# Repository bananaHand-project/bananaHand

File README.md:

---

**BananaHand** is an open-source 16 DOF/6 DOA humanoid hand designed for physical AI research and deployment on light-weight robot arms.

BananaHand features human-like proportions with no fore-arm, up to 4lb payload capacity, integrated palm and finger tip FSR based force sensing, and a low BOM cost of $900USD.

With the project being open-source as a top priority, all resources used in the creation are freely available and open-source themselves (KiCad, OnShape, Foxglove, Embassy-rs, etc.).

*We're in continuous development and actively seeking contributors, research partners, and company collaborators to shape the next generation of practical humanoid systems. Ready to join the future of open-source robotics?*

## Repo Structure

- [`docs/`](./docs/) contains build instructions, getting started guide, and more.
- [`firmware/`](./firmware/) contains the code that runs on the bananaHand main board.
  - [`firmware/primary-g474/`](./firmware/primary-g474/) contains the firmware run on the primary MCU (stm32g474).
  - [`firmware/sensing-c071/`](./firmware/sensing-c071/) contains the firmware run on the sensing MCU (stm32c071).
  - [`firmware/common/`](./firmware/common/) contains code used by both MCUs.
  - [`firmware/experiments/`](./firmware/experiments/) contains code used in the development of the hand.
- [`hardware/`](./hardware/) contains both electrical and mechanical CAD models, BOMs, and detailed descriptions.
- [`software/`](./software/) contains ROS and Foxglove implementations.

---
***We can't wait to see what you grasp!***

Made with ❤️ in 🇨🇦 at 🪿.

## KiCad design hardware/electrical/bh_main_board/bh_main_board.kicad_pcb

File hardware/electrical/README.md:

# Electrical

The electrical system for bananaHand is built around the main board. The main board is responsible for the following functions: communication with the controlling device, motor control, and FSR sensing. A simplified block diagram describing the main board can be seen below. It requires a single +12V 24W input source and exposes UART, CAN bus, and half-duplex RS485 options for interfacing. Depending on the device you are trying to interface with, a buck converter may be needed to drop your source voltage down to the required 12V.

## Main Board

The main board has the following sub-circuits:

- **Micro-controllers**: There are two MCUs on the main board. The first is the stm32g474, responsible for communication with the upstream device and motor control. The second micro-controller is the stm32c071, which acts as a "smart" ADC, filtering and forwarding force readings to the stm32g4.
- **Power stage**: Basic fuse protection, and a MPM3610 buck converter for 12V -> 3V3 for logic level ICs
- **Motor driving**: There are eight DRV8876 motor driver circuits for the [PQ12P](https://www.actuonix.com/pq12-30-12-p). The driving circuits are controlled and motor positions are read by the stm32g474 micro-controller.
- **Force sensing**: Simple linear voltage divider circuits are used to interface with the force sensitive resistors. Their voltages are read by the 2nd micro-controller on board the stm32c071
- **Communication interfaces**: There are three communication interfaces exposed by the board: CAN Bus, UART, and half-duplex RS485.

### Schematic

A full PDF of the schematic can be found in `bh_main_board/bananaHand_main_board_sch.pdf` or linked [here](./bh_main_board/bananaHand_main_board_sch.pdf).

### Layout

**Four layer:** Sig, GND, GND/PWR, Sig

### Known Flaws

#### V0.1.0

No issues that impact the performance of the board or require re-work.

- The silkscreen on the back labelling the PQ12P connectors for Index1 and Index 2 are flipped.
- Index 2 breaks the convention of the HRTIM channel connections to DRV8876 with `IN1 <-> CH1` and `IN2 <-> CH2` (instead of `IN1 <-> CH2` and `IN2 <-> CH1` like all other fingers).

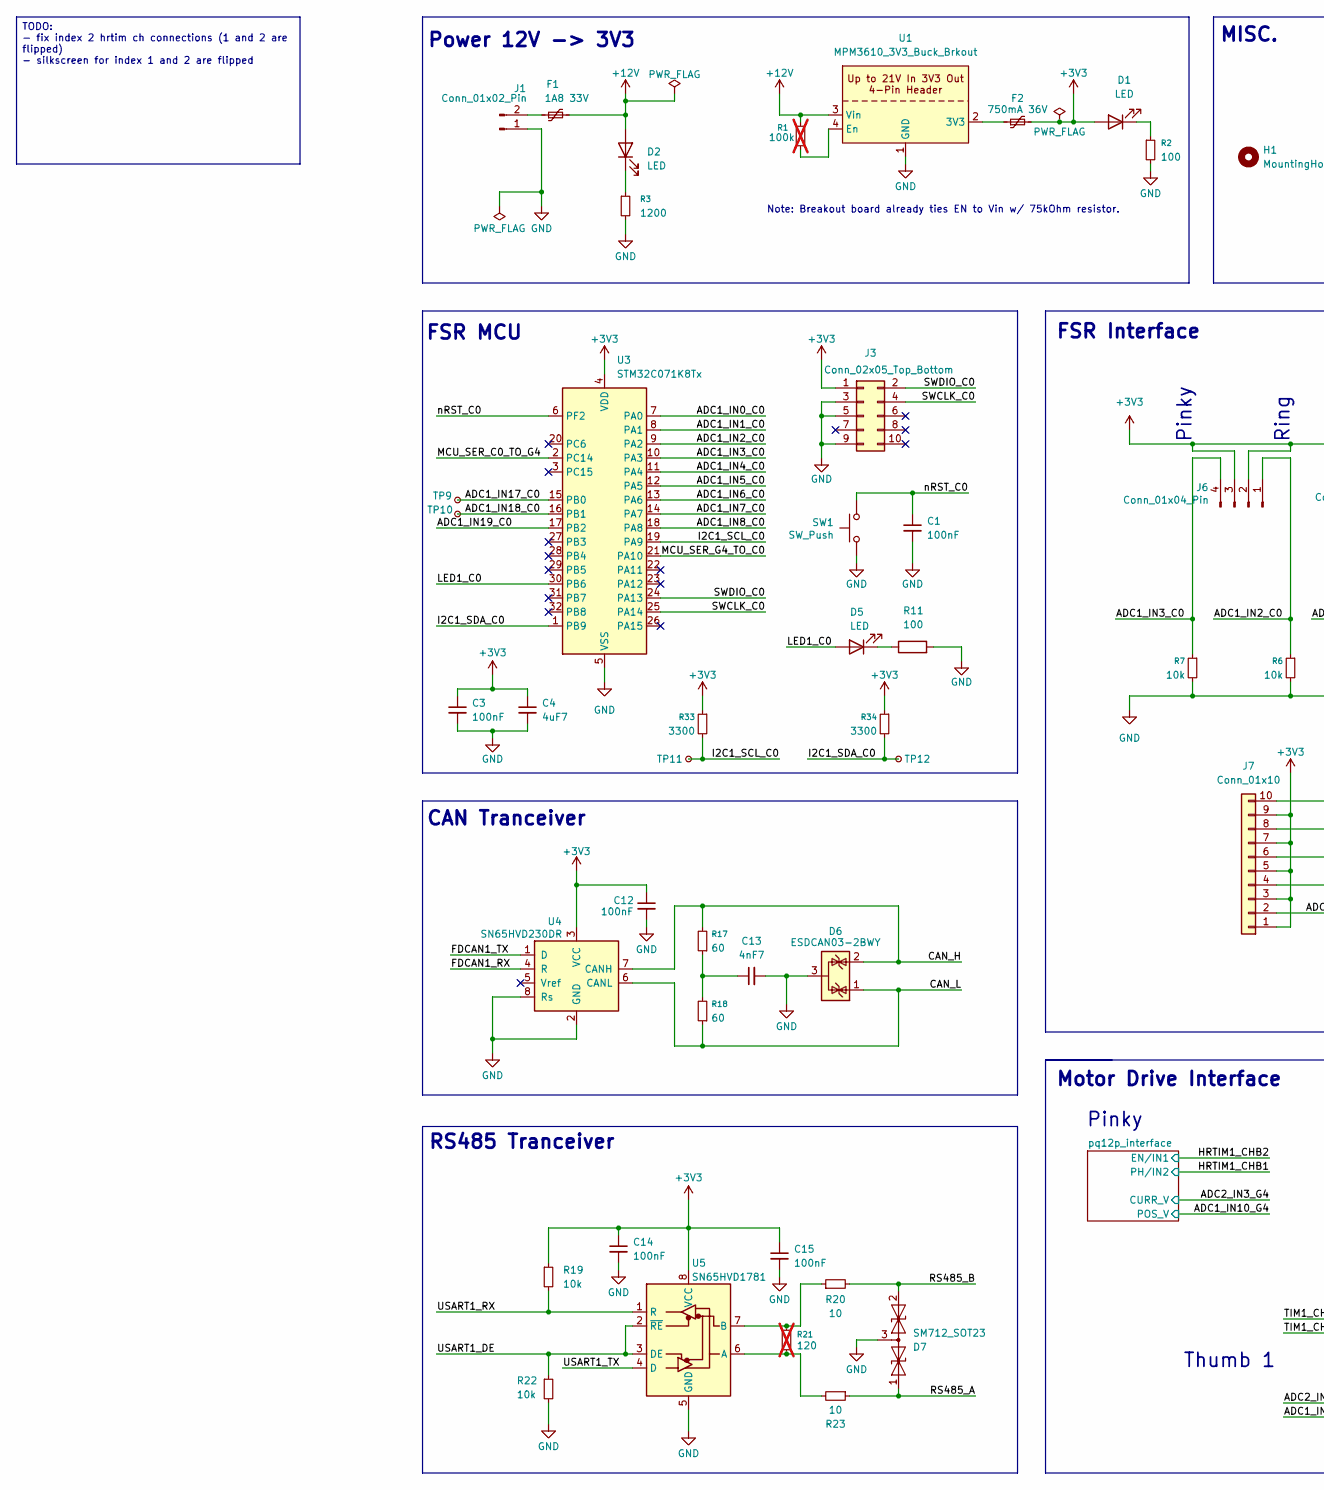
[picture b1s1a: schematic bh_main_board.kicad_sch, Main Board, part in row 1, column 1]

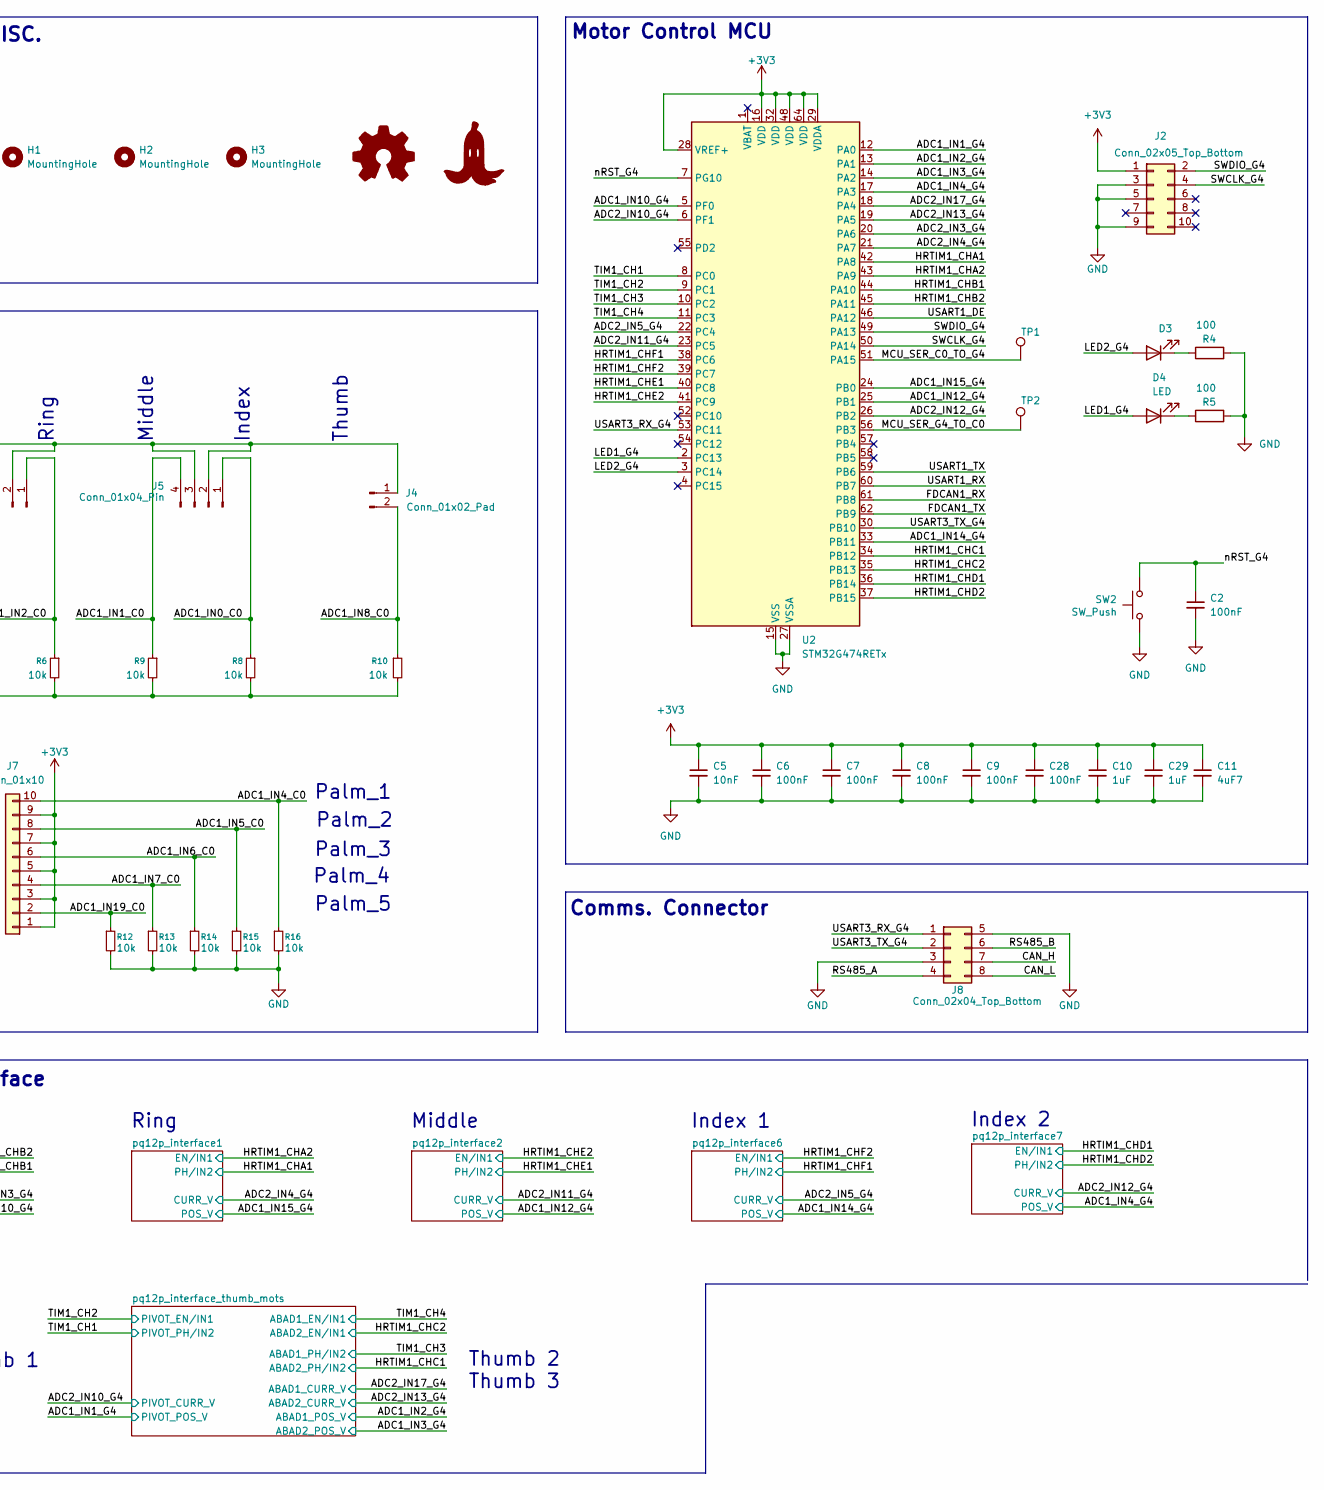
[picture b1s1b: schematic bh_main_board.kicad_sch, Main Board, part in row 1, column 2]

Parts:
ART1: mk_banana_footprint
ART2: Logo_Open_Hardware_Small; OSHW-Logo2_9.8x8mm_SilkScreen
C1, C2, C3, C6, C7, C8, C9, C12, C14, C15, C28: 100nF; C_0402_1005Metric; MFR # GRM155R71H104KE14D; LCSC # C77020
C4, C11: 4uF7; C_0603_1608Metric_Pad1.08x0.95mm_HandSolder; MFR # GRM188R6YA475KE15D; LCSC # C162274
C5: 10nF; C_0402_1005Metric; MFR # GRM155R71H103KA88D; LCSC # C77019
C10, C29: 1uF; C_0603_1608Metric_Pad1.08x0.95mm_HandSolder; MFR # GCM188R71E105KA64D; LCSC # C85862
C13: 4nF7; C_0402_1005Metric; MFR # GRM1555C1H472JE01D; LCSC # C1518204
D1, D2, D3, D4, D5: LED; LED_0402_1005Metric_Pad0.77x0.64mm_HandSolder; MFR # XL-1005UYC; LCSC # C25503856
D6: ESDCAN03-2BWY; SOT-323_SC-70; MFR # ESDCAN03-2BWY; LCSC # C1973833
D7: SM712_SOT23; SOT-23; MFR # SM712-02HTG; LCSC # C172881
F1: 1A8 33V; Fuse_1206_3216Metric_Pad1.42x1.75mm_HandSolder; MFR # YTL 1206L100/33V; LCSC # C49318377
F2: 750mA 36V; Fuse_1206_3216Metric; MFR # 1206L075/36NR; LCSC # C49196638
H1, H2, H3: MountingHole; MountingHole_2.7mm_Pad_Via
J1: Conn_01x02_Pin; AMASS_XT30UPB-M_1x02_P5.0mm_Vertical; MFR # XT30UPB-M; LCSC # C428721
J2, J3: Conn_02x05_Top_Bottom; PinHeader_2x05_P1.27mm_Vertical; MFR # ZX-PZ1.27-2-5PZZ; LCSC # C7501289
J4: Conn_01x02_Pad; JST_ZH_B2B-ZR_1x02_P1.50mm_Vertical; MFR # JST B2B-ZR(LF)(SN); LCSC # C158011
J5, J6: Conn_01x04_Pin; JST_ZH_B4B-ZR_1x04_P1.50mm_Vertical; MFR # JST B4B-ZR(LF)(SN); LCSC # C157997
J7: Conn_01x10; JST_ZH_B10B-ZR_1x10_P1.50mm_Vertical; MFR # B10B-ZR(LF)(SN); LCSC # C158036
J8: Conn_02x04_Top_Bottom; JST_PHD_B8B-PHDSS_2x04_P2.00mm_Vertical; MFR # B8B-PHDSS(LF)(SN); LCSC # C157975
R1: 100k; R_0603_1608Metric_Pad0.98x0.95mm_HandSolder; MFR # RC0603FR-07100KL; LCSC # C14675; not fitted
R2, R4, R5, R11: 100; R_0402_1005Metric_Pad0.72x0.64mm_HandSolder; MFR # ERJ2RKF1000X; LCSC # C413063
R3: 1200; R_0603_1608Metric_Pad0.98x0.95mm_HandSolder; MFR # RC0603FR-071K2L; LCSC # C114605
R6, R7, R8, R9, R10, R12, R13, R14, R15, R16, R19, R22: 10k; R_0402_1005Metric_Pad0.72x0.64mm_HandSolder; MFR # RT0402BRD0710KL; LCSC # C190095
R17, R18: 60; R_0603_1608Metric_Pad0.98x0.95mm_HandSolder; MFR # 0603WAF604JT5E; LCSC # C23090
R20, R23: 10; R_0603_1608Metric_Pad0.98x0.95mm_HandSolder; MFR # RC0603FR-0710RL; LCSC # C109318
R21: 120; R_0603_1608Metric_Pad0.98x0.95mm_HandSolder; MFR # RC0603FR-07120RL; LCSC # C114640; not fitted
R33, R34: 3300; R_0402_1005Metric_Pad0.72x0.64mm_HandSolder; MFR # RC0402FR-073K3L; LCSC # C137992
SW1, SW2: SW_Push; SW_SPST_TS-1088-xR025; MFR # TS-1088R-02526; LCSC # C455281
TP1, TP2: TestPoint; TestPoint_Pad_D1.0mm
TP9, TP10, TP11, TP12: TestPoint_Small; TestPoint_Pad_D2.0mm
U1: MPM3610_3V3_Buck_Brkout; MP3610_3V3_BUCK_BREAKOUT
U2: STM32G474RETx; LQFP-64_10x10mm_P0.5mm; MFR # STM32G474RET6; LCSC # C521608
U3: STM32C071K8Tx; LQFP-32_7x7mm_P0.8mm; MFR # STM32C071K8T6; LCSC # C43650208
U4: SN65HVD230DR; SOIC-8_3.9x4.9mm_P1.27mm; MFR # SN65HVD230DR; LCSC # C12084
U5: SN65HVD1781; SOIC-8_3.9x4.9mm_P1.27mm; MFR # SN65HVD1781DR; LCSC # C42737

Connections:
+3V3: C3.1, C4.1, C5.1, C6.1, C7.1, C8.1, C9.1, C10.1, C11.1, C12.1, C14.1, C15.1, C28.1, C29.1, D1.2 (A), F2.2, J2.1, J3.1, J4.1, J5.2, J5.3, J6.2, J6.3, J7.1, J7.3, J7.5, J7.7, J7.9, R19.1, R33.1, R34.1, U2.16 (VDD), U2.28 (VREF+), U2.29 (VDDA), U2.32 (VDD), U2.48 (VDD), U2.64 (VDD), U3.4 (VDD), U4.3 (VCC), U5.8 (VCC); also elsewhere on the board
+12V: D2.2 (A), F1.2, R1.1, U1.3 (Vin); also elsewhere on the board
/ADC1_IN0_C0: J5.1, R8.1, U3.7 (PA0)
/ADC1_IN1_C0: J5.4, R9.1, U3.8 (PA1)
/ADC1_IN1_G4: U2.12 (PA0); also elsewhere on the board
/ADC1_IN2_C0: J6.1, R6.1, U3.9 (PA2)
/ADC1_IN2_G4: U2.13 (PA1); also elsewhere on the board
/ADC1_IN3_C0: J6.4, R7.1, U3.10 (PA3)
/ADC1_IN3_G4: U2.14 (PA2); also elsewhere on the board
/ADC1_IN4_C0: J7.10, R16.1, U3.11 (PA4)
/ADC1_IN4_G4: U2.17 (PA3); also elsewhere on the board
/ADC1_IN5_C0: J7.8, R15.1, U3.12 (PA5)
/ADC1_IN6_C0: J7.6, R14.1, U3.13 (PA6)
/ADC1_IN7_C0: J7.4, R13.1, U3.14 (PA7)
/ADC1_IN8_C0: J4.2, R10.1, U3.18 (PA8)
/ADC1_IN10_G4: U2.5 (PF0); also elsewhere on the board
/ADC1_IN12_G4: U2.25 (PB1); also elsewhere on the board
/ADC1_IN14_G4: U2.33 (PB11); also elsewhere on the board
/ADC1_IN15_G4: U2.24 (PB0); also elsewhere on the board
/ADC1_IN17_C0: TP9.1, U3.15 (PB0)
/ADC1_IN18_C0: TP10.1, U3.16 (PB1)
/ADC1_IN19_C0: J7.2, R12.1, U3.17 (PB2)
/ADC2_IN3_G4: U2.20 (PA6); also elsewhere on the board
/ADC2_IN4_G4: U2.21 (PA7); also elsewhere on the board
/ADC2_IN5_G4: U2.22 (PC4); also elsewhere on the board
/ADC2_IN10_G4: U2.6 (PF1); also elsewhere on the board
/ADC2_IN11_G4: U2.23 (PC5); also elsewhere on the board
/ADC2_IN12_G4: U2.26 (PB2); also elsewhere on the board
/ADC2_IN13_G4: U2.19 (PA5); also elsewhere on the board
/ADC2_IN17_G4: U2.18 (PA4); also elsewhere on the board
/CAN_H: D6.2 (K), J8.7, R17.2, U4.7 (CANH)
/CAN_L: D6.1 (K), J8.8, R18.1, U4.6 (CANL)
/FDCAN1_RX: U2.61 (PB8), U4.4 (R)
/FDCAN1_TX: U2.62 (PB9), U4.1 (D)
/HRTIM1_CHA1: U2.42 (PA8); also elsewhere on the board
/HRTIM1_CHA2: U2.43 (PA9); also elsewhere on the board
/HRTIM1_CHB1: U2.44 (PA10); also elsewhere on the board
/HRTIM1_CHB2: U2.45 (PA11); also elsewhere on the board
/HRTIM1_CHC1: U2.34 (PB12); also elsewhere on the board
/HRTIM1_CHC2: U2.35 (PB13); also elsewhere on the board
/HRTIM1_CHD1: U2.36 (PB14); also elsewhere on the board
/HRTIM1_CHD2: U2.37 (PB15); also elsewhere on the board
/HRTIM1_CHE1: U2.40 (PC8); also elsewhere on the board
/HRTIM1_CHE2: U2.41 (PC9); also elsewhere on the board
/HRTIM1_CHF1: U2.38 (PC6); also elsewhere on the board
/HRTIM1_CHF2: U2.39 (PC7); also elsewhere on the board
/I2C1_SCL_C0: R33.2, TP11.1, U3.19 (PA9)
/I2C1_SDA_C0: R34.2, TP12.1, U3.1 (PB9)
/LED1_C0: D5.2 (A), U3.30 (PB6)
/LED1_G4: D4.2 (A), U2.2 (PC13)
/LED2_G4: D3.2 (A), U2.3 (PC14)
/MCU_SER_C0_TO_G4: TP1.1, U2.51 (PA15), U3.2 (PC14)
/MCU_SER_G4_TO_C0: TP2.1, U2.56 (PB3), U3.21 (PA10)
/RS485_A: D7.1 (A1), J8.4, R23.1
/RS485_B: D7.2 (A2), J8.6, R20.2
/SWCLK_C0: J3.4, U3.25 (PA14)
/SWCLK_G4: J2.4, U2.50 (PA14)
/SWDIO_C0: J3.2, U3.24 (PA13)
/SWDIO_G4: J2.2, U2.49 (PA13)
/TIM1_CH1: U2.8 (PC0); also elsewhere on the board
/TIM1_CH2: U2.9 (PC1); also elsewhere on the board
/TIM1_CH3: U2.10 (PC2); also elsewhere on the board
/TIM1_CH4: U2.11 (PC3); also elsewhere on the board
/USART1_DE: R22.1, U2.46 (PA12), U5.2 (~RE), U5.3 (DE)
/USART1_RX: R19.2, U2.60 (PB7), U5.1 (R)
/USART1_TX: U2.59 (PB6), U5.4 (D)
/USART3_RX_G4: J8.1, U2.53 (PC11)
/USART3_TX_G4: J8.2, U2.30 (PB10)
/nRST_C0: C1.1, SW1.2, U3.6 (PF2)
/nRST_G4: C2.1, SW2.2, U2.7 (PG10)
GND: C1.2, C2.2, C3.2, C4.2, C5.2, C6.2, C7.2, C8.2, C9.2, C10.2, C11.2, C12.2, C13.2, C14.2, C15.2, C28.2, C29.2, D6.3 (A), D7.3 (common), J1.1, J2.3, J2.5, J2.9, J3.3, J3.5, J3.9, J8.3, J8.5, R2.2, R3.2, R4.2, R5.2, R6.2, R7.2, R8.2, R9.2, R10.2, R11.2, R12.2, R13.2, R14.2, R15.2, R16.2, R22.2, SW1.1, SW2.1, U1.1 (GND), U2.15 (VSS), U2.27 (VSSA), U2.31 (VSS), U2.47 (VSS), U2.63 (VSS), U3.5 (VSS), U4.2 (GND), U4.8 (Rs), U5.5 (GND); also elsewhere on the board
unnamed: C13.1, R17.1, R18.2
unnamed: D1.1 (K), R2.1
unnamed: D2.1 (K), R3.1
unnamed: D3.1 (K), R4.1
unnamed: D4.1 (K), R5.1
unnamed: D5.1 (K), R11.1
unnamed: F1.1, J1.2
unnamed: F2.1, U1.2 (3V3)
unnamed: R1.2, U1.4 (En)
unnamed: R21.2, R23.2, U5.6 (A)
unnamed: R20.1, R21.1, U5.7 (B)

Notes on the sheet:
Motor Drive Interface
Palm_3
Thumb 2
Pinky
Thumb 3
Index 2
CAN Tranceiver
FSR Interface
Palm_4
Motor Control MCU
RS485 Tranceiver
Middle
Comms. Connector
Ring
Thumb 1
Palm_5
Note: Breakout board already ties EN to Vin w/ 75kOhm resistor.
Power 12V -> 3V3
Index
Palm_1
MISC.
FSR MCU
Palm_2
Index 1
Thumb
TODO: - fix index 2 hrtim ch connections (1 and 2 are flipped) - silkscreen for index 1 and 2 are flipped

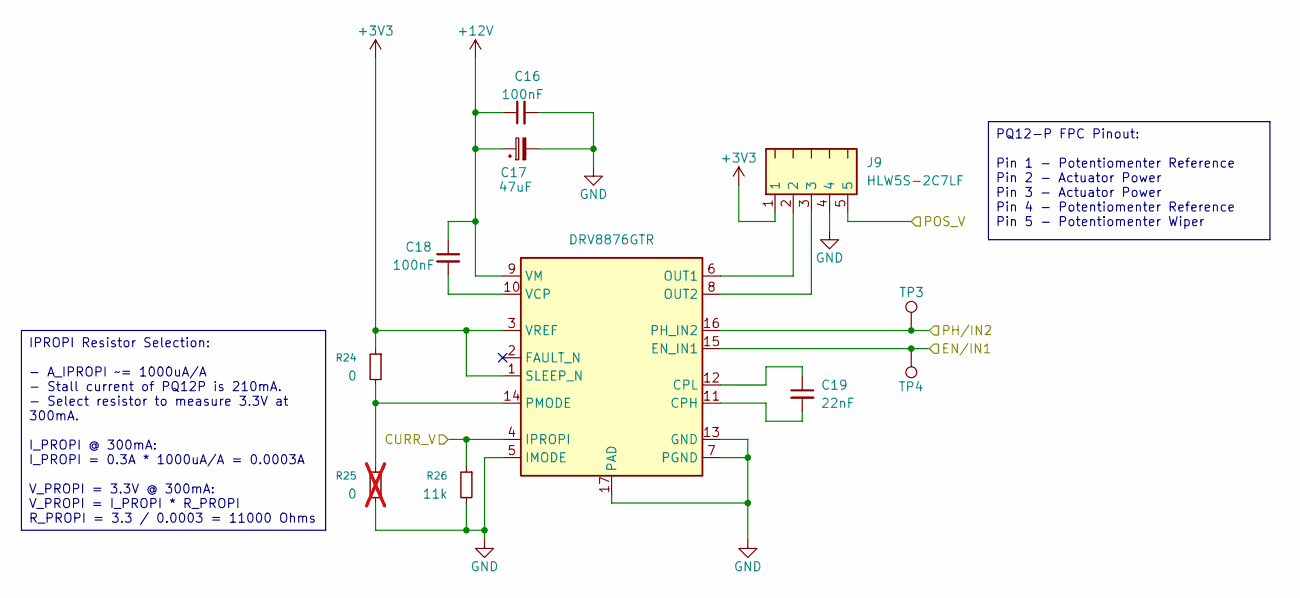
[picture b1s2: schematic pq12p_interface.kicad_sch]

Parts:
C16, C18: 100nF; C_0402_1005Metric; MFR # GRM155R71H104KE14D; LCSC # C77020
C17: 47uF; CP_Elec_6.3x5.8; MFR # EEEFP1V470AP; LCSC # C401754
C19: 22nF; C_0402_1005Metric; MFR # GRM155R71H223KA12D; LCSC # C77023
J9: HLW5S-2C7LF; MFR # HLW5S-2C7LF; LCSC # C5406437
R24: 0; R_0603_1608Metric_Pad0.98x0.95mm_HandSolder; MFR # RC0603JR-070RL; LCSC # C95177
R25: 0; R_0603_1608Metric_Pad0.98x0.95mm_HandSolder; MFR # RC0603JR-070RL; LCSC # C95177; not fitted
R26: 11k; R_0402_1005Metric_Pad0.72x0.64mm_HandSolder; MFR # RT0402BRE0711KL; LCSC # C705643
TP3, TP4: TestPoint; TestPoint_Pad_D1.0mm
U6: DRV8876GTR; DRV8876GTR-MFG; MFR # DRV8876RGTR; LCSC # C1852100

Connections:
+3V3: J9.1, R24.1, U6.1 (SLEEP_N), U6.3 (VREF); also elsewhere on the board
+12V: C16.1, C17.1, C18.1, U6.9 (VM); also elsewhere on the board
/ADC1_IN10_G4: J9.5; also elsewhere on the board
/ADC2_IN3_G4: R26.1, U6.4 (IPROPI); also elsewhere on the board
/HRTIM1_CHB1: TP3.1, U6.16 (PH_IN2); also elsewhere on the board
/HRTIM1_CHB2: TP4.1, U6.15 (EN_IN1); also elsewhere on the board
GND: C16.2, C17.2, J9.4, R25.2, R26.2, U6.5 (IMODE), U6.7 (PGND), U6.13 (GND), U6.17 (PAD), U6.18, U6.19, U6.20, U6.21, U6.22; also elsewhere on the board
unnamed: C19.2, U6.11 (CPH)
unnamed: C19.1, U6.12 (CPL)
unnamed: J9.2, U6.6 (OUT1)
unnamed: J9.3, U6.8 (OUT2)
unnamed: R24.2, R25.1, U6.14 (PMODE)
unnamed: C18.2, U6.10 (VCP)

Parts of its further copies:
C20, C22, C24, C26, C36, C38, C40, C42: 100nF; C_0402_1005Metric; MFR # GRM155R71H104KE14D; LCSC # C77020
C21, C25, C37, C41: 47uF; CP_Elec_6.3x5.8; MFR # EEEFP1V470AP; LCSC # C401754
C23, C27, C39, C43: 22nF; C_0402_1005Metric; MFR # GRM155R71H223KA12D; LCSC # C77023
J10, J11, J12, J13: HLW5S-2C7LF; MFR # HLW5S-2C7LF; LCSC # C5406437
R27, R30, R39, R42: 0; R_0603_1608Metric_Pad0.98x0.95mm_HandSolder; MFR # RC0603JR-070RL; LCSC # C95177
R28, R31, R40, R43: 0; R_0603_1608Metric_Pad0.98x0.95mm_HandSolder; MFR # RC0603JR-070RL; LCSC # C95177; not fitted
R29, R32, R41, R44: 11k; R_0402_1005Metric_Pad0.72x0.64mm_HandSolder; MFR # RT0402BRE0711KL; LCSC # C705643
TP5, TP6, TP7, TP8, TP13, TP14, TP15, TP16: TestPoint; TestPoint_Pad_D1.0mm
U7, U8, U11, U12: DRV8876GTR; DRV8876GTR-MFG; MFR # DRV8876RGTR; LCSC # C1852100

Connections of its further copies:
+3V3: J10.1, J11.1, J12.1, J13.1, R27.1, R30.1, R39.1, R42.1, U7.1 (SLEEP_N), U7.3 (VREF), U8.1 (SLEEP_N), U8.3 (VREF), U11.1 (SLEEP_N), U11.3 (VREF), U12.1 (SLEEP_N), U12.3 (VREF); also elsewhere on the board
+12V: C20.1, C21.1, C22.1, C24.1, C25.1, C26.1, C36.1, C37.1, C38.1, C40.1, C41.1, C42.1, U7.9 (VM), U8.9 (VM), U11.9 (VM), U12.9 (VM); also elsewhere on the board
/ADC1_IN4_G4: J13.5; also elsewhere on the board
/ADC1_IN12_G4: J11.5; also elsewhere on the board
/ADC1_IN14_G4: J12.5; also elsewhere on the board
/ADC1_IN15_G4: J10.5; also elsewhere on the board
/ADC2_IN4_G4: R29.1, U7.4 (IPROPI); also elsewhere on the board
/ADC2_IN5_G4: R41.1, U11.4 (IPROPI); also elsewhere on the board
/ADC2_IN11_G4: R32.1, U8.4 (IPROPI); also elsewhere on the board
/ADC2_IN12_G4: R44.1, U12.4 (IPROPI); also elsewhere on the board
/HRTIM1_CHA1: TP5.1, U7.16 (PH_IN2); also elsewhere on the board
/HRTIM1_CHA2: TP6.1, U7.15 (EN_IN1); also elsewhere on the board
/HRTIM1_CHD1: TP16.1, U12.15 (EN_IN1); also elsewhere on the board
/HRTIM1_CHD2: TP15.1, U12.16 (PH_IN2); also elsewhere on the board
/HRTIM1_CHE1: TP7.1, U8.16 (PH_IN2); also elsewhere on the board
/HRTIM1_CHE2: TP8.1, U8.15 (EN_IN1); also elsewhere on the board
/HRTIM1_CHF1: TP13.1, U11.16 (PH_IN2); also elsewhere on the board
/HRTIM1_CHF2: TP14.1, U11.15 (EN_IN1); also elsewhere on the board
GND: C20.2, C21.2, C24.2, C25.2, C36.2, C37.2, C40.2, C41.2, J10.4, J11.4, J12.4, J13.4, R28.2, R29.2, R31.2, R32.2, R40.2, R41.2, R43.2, R44.2, U7.5 (IMODE), U7.7 (PGND), U7.13 (GND), U7.17 (PAD), U7.18, U7.19, U7.20, U7.21, U7.22, U8.5 (IMODE), U8.7 (PGND), U8.13 (GND), U8.17 (PAD), U8.18, U8.19, U8.20, U8.21, U8.22, U11.5 (IMODE), U11.7 (PGND), U11.13 (GND), U11.17 (PAD), U11.18, U11.19, U11.20, U11.21, U11.22, U12.5 (IMODE), U12.7 (PGND), U12.13 (GND), U12.17 (PAD), U12.18, U12.19, U12.20, U12.21, U12.22; also elsewhere on the board
unnamed: C23.2, U7.11 (CPH)
unnamed: C23.1, U7.12 (CPL)
unnamed: J10.2, U7.6 (OUT1)
unnamed: J10.3, U7.8 (OUT2)
unnamed: R27.2, R28.1, U7.14 (PMODE)
unnamed: C22.2, U7.10 (VCP)
unnamed: C27.2, U8.11 (CPH)
unnamed: C27.1, U8.12 (CPL)
unnamed: J11.2, U8.6 (OUT1)
unnamed: J11.3, U8.8 (OUT2)
unnamed: R30.2, R31.1, U8.14 (PMODE)
unnamed: C26.2, U8.10 (VCP)
unnamed: C39.2, U11.11 (CPH)
unnamed: C39.1, U11.12 (CPL)
unnamed: J12.2, U11.6 (OUT1)
unnamed: J12.3, U11.8 (OUT2)
unnamed: R39.2, R40.1, U11.14 (PMODE)
unnamed: C38.2, U11.10 (VCP)
unnamed: C43.2, U12.11 (CPH)
unnamed: C43.1, U12.12 (CPL)
unnamed: J13.2, U12.6 (OUT1)
unnamed: J13.3, U12.8 (OUT2)
unnamed: R42.2, R43.1, U12.14 (PMODE)
unnamed: C42.2, U12.10 (VCP)

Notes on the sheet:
PQ12-P FPC Pinout: Pin 1 - Potentiomenter Reference Pin 2 - Actuator Power Pin 3 - Actuator Power Pin 4 - Potentiomenter Reference Pin 5 - Potentiomenter Wiper
IPROPI Resistor Selection: - A_IPROPI ~= 1000uA/A - Stall current of PQ12P is 210mA. - Select resistor to measure 3.3V at 300mA. I_PROPI @ 300mA: I_PROPI = 0.3A * 1000uA/A = 0.0003A V_PROPI = 3.3V @ 300mA: V_PROPI = I_PROPI * R_PROPI R_PROPI = 3.3 / 0.0003 = 11000 Ohms

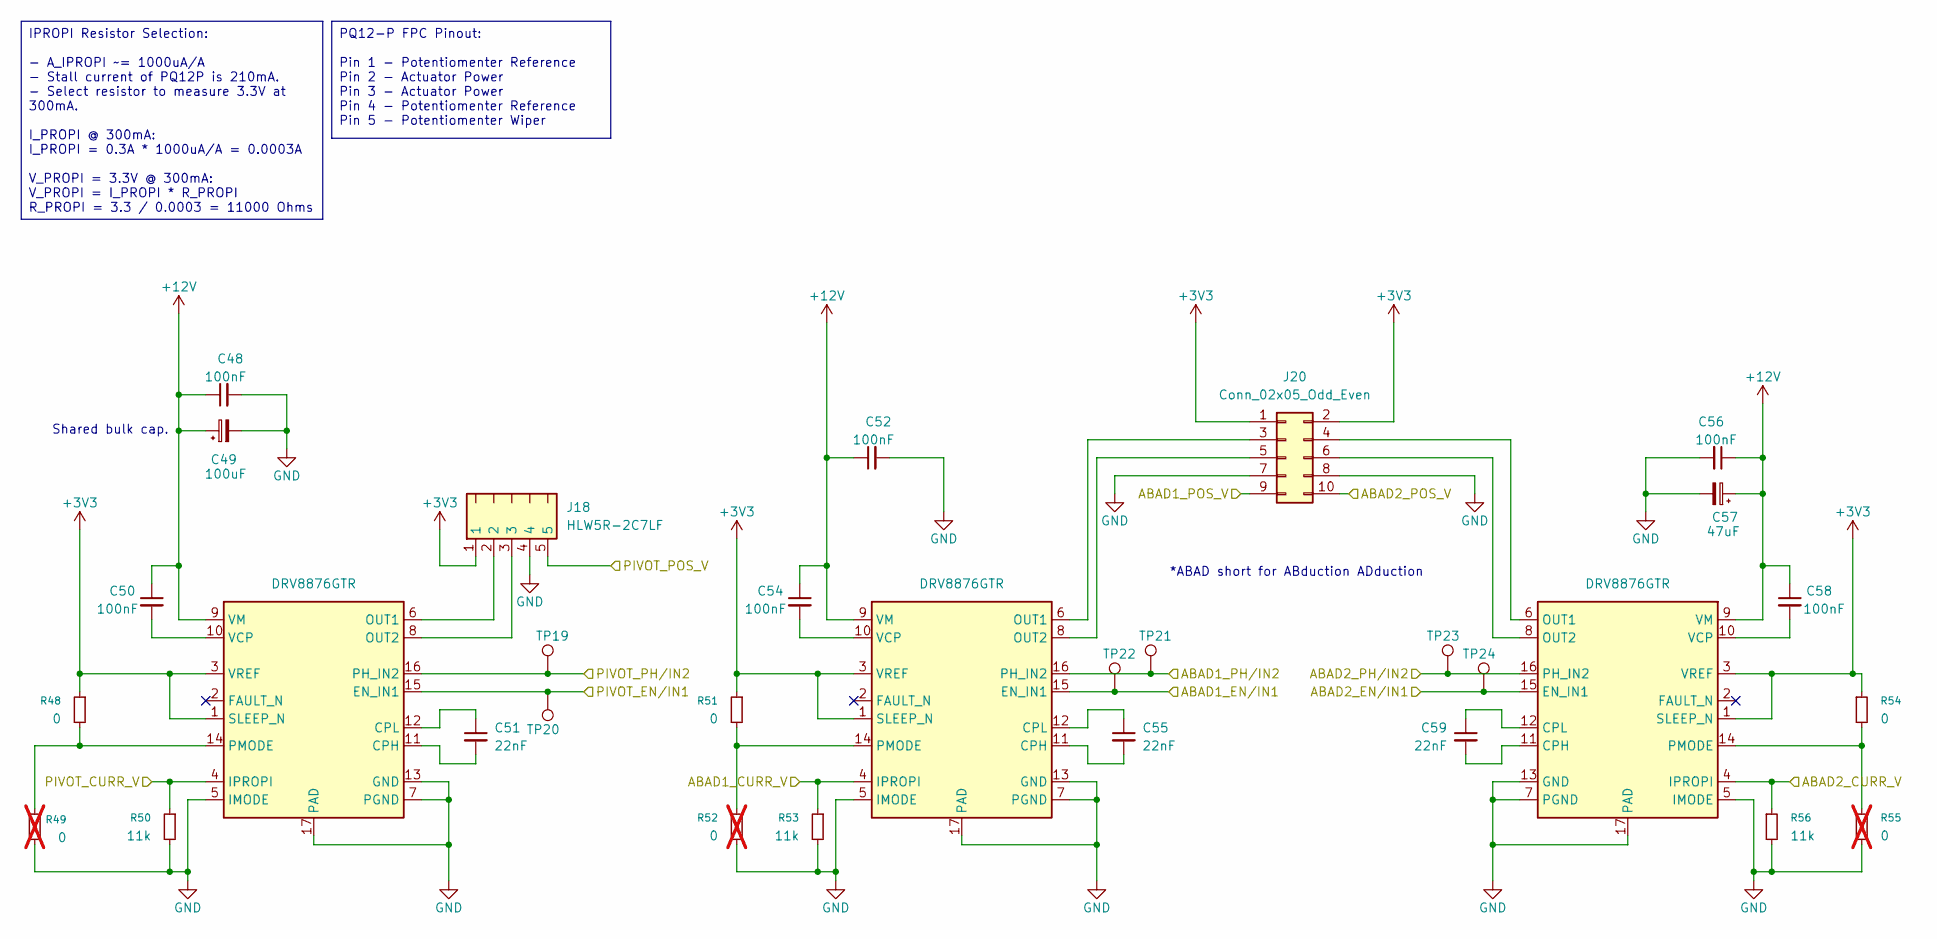
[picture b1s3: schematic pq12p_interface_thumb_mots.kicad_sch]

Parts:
C48, C50, C52, C54, C56, C58: 100nF; C_0402_1005Metric; MFR # GRM155R71H104KE14D; LCSC # C77020
C49: 100uF; CP_Elec_6.3x5.8; MFR # EEEFT1V101AP; LCSC # C128464
C51, C55, C59: 22nF; C_0402_1005Metric; MFR # GRM155R71H223KA12D; LCSC # C77023
C57: 47uF; CP_Elec_6.3x5.8; MFR # EEEFP1V470AP; LCSC # C401754
J18: HLW5R-2C7LF; MFR # HLW5R-2C7LF; LCSC # C5406452
J20: Conn_02x05_Odd_Even; JST_PHD_B10B-PHDSS_2x05_P2.00mm_Vertical; MFR # B10B-PHDSS(LF)(SN); LCSC # C471519
R48, R51, R54: 0; R_0603_1608Metric_Pad0.98x0.95mm_HandSolder; MFR # RC0603JR-070RL; LCSC # C95177
R49, R52, R55: 0; R_0603_1608Metric_Pad0.98x0.95mm_HandSolder; MFR # RC0603JR-070RL; LCSC # C95177; not fitted
R50, R53, R56: 11k; R_0402_1005Metric_Pad0.72x0.64mm_HandSolder; MFR # RT0402BRE0711KL; LCSC # C705643
TP19, TP20, TP21, TP22, TP23, TP24: TestPoint; TestPoint_Pad_D1.0mm
U14, U15, U16: DRV8876GTR; DRV8876GTR-MFG; MFR # DRV8876RGTR; LCSC # C1852100

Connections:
+3V3: J18.1, J20.1, J20.2, R48.1, R51.1, R54.1, U14.1 (SLEEP_N), U14.3 (VREF), U15.1 (SLEEP_N), U15.3 (VREF), U16.1 (SLEEP_N), U16.3 (VREF); also elsewhere on the board
+12V: C48.1, C49.1, C50.1, C52.1, C54.1, C56.1, C57.1, C58.1, U14.9 (VM), U15.9 (VM), U16.9 (VM); also elsewhere on the board
/ADC1_IN1_G4: J18.5; also elsewhere on the board
/ADC1_IN2_G4: J20.9; also elsewhere on the board
/ADC1_IN3_G4: J20.10; also elsewhere on the board
/ADC2_IN10_G4: R50.1, U14.4 (IPROPI); also elsewhere on the board
/ADC2_IN13_G4: R56.1, U16.4 (IPROPI); also elsewhere on the board
/ADC2_IN17_G4: R53.1, U15.4 (IPROPI); also elsewhere on the board
/HRTIM1_CHC1: TP23.1, U16.16 (PH_IN2); also elsewhere on the board
/HRTIM1_CHC2: TP24.1, U16.15 (EN_IN1); also elsewhere on the board
/TIM1_CH1: TP19.1, U14.16 (PH_IN2); also elsewhere on the board
/TIM1_CH2: TP20.1, U14.15 (EN_IN1); also elsewhere on the board
/TIM1_CH3: TP21.1, U15.16 (PH_IN2); also elsewhere on the board
/TIM1_CH4: TP22.1, U15.15 (EN_IN1); also elsewhere on the board
GND: C48.2, C49.2, C52.2, C56.2, C57.2, J18.4, J20.7, J20.8, R49.2, R50.2, R52.2, R53.2, R55.2, R56.2, U14.5 (IMODE), U14.7 (PGND), U14.13 (GND), U14.17 (PAD), U14.18, U14.19, U14.20, U14.21, U14.22, U15.5 (IMODE), U15.7 (PGND), U15.13 (GND), U15.17 (PAD), U15.18, U15.19, U15.20, U15.21, U15.22, U16.5 (IMODE), U16.7 (PGND), U16.13 (GND), U16.17 (PAD), U16.18, U16.19, U16.20, U16.21, U16.22; also elsewhere on the board
unnamed: J20.3, U15.6 (OUT1)
unnamed: J20.4, U16.6 (OUT1)
unnamed: J20.5, U15.8 (OUT2)
unnamed: J20.6, U16.8 (OUT2)
unnamed: C51.2, U14.11 (CPH)
unnamed: C51.1, U14.12 (CPL)
unnamed: J18.2, U14.6 (OUT1)
unnamed: J18.3, U14.8 (OUT2)
unnamed: R48.2, R49.1, U14.14 (PMODE)
unnamed: C50.2, U14.10 (VCP)
unnamed: C55.2, U15.11 (CPH)
unnamed: C55.1, U15.12 (CPL)
unnamed: R51.2, R52.1, U15.14 (PMODE)
unnamed: C54.2, U15.10 (VCP)
unnamed: C59.2, U16.11 (CPH)
unnamed: C59.1, U16.12 (CPL)
unnamed: R54.2, R55.1, U16.14 (PMODE)
unnamed: C58.2, U16.10 (VCP)

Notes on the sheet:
*ABAD short for ABduction ADduction
Shared bulk cap.
PQ12-P FPC Pinout: Pin 1 - Potentiomenter Reference Pin 2 - Actuator Power Pin 3 - Actuator Power Pin 4 - Potentiomenter Reference Pin 5 - Potentiomenter Wiper
IPROPI Resistor Selection: - A_IPROPI ~= 1000uA/A - Stall current of PQ12P is 210mA. - Select resistor to measure 3.3V at 300mA. I_PROPI @ 300mA: I_PROPI = 0.3A * 1000uA/A = 0.0003A V_PROPI = 3.3V @ 300mA: V_PROPI = I_PROPI * R_PROPI R_PROPI = 3.3 / 0.0003 = 11000 Ohms
